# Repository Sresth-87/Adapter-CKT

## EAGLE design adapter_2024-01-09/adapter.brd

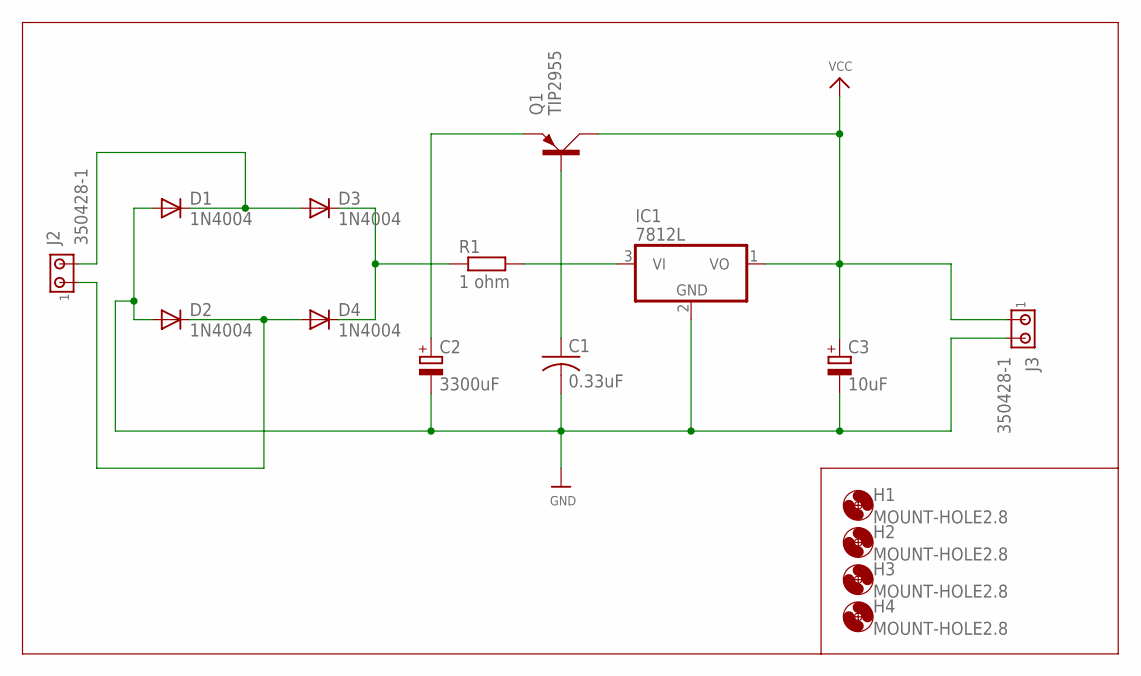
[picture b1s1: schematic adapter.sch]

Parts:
C1: 0.33uF; C025-024X044
C2: 3300uF; CAPPRD508W65D1000H1100B
C3: 10uF; CAPPRD508W65D1000H1100B
D1, D2, D3, D4: 1N4004; DO41-10
H1, H2, H3, H4: MOUNT-HOLE2.8; 2,8
IC1: 7812L; TO92
J2, J3: 350428-1
Q1: TIP2955; TOP3AV
R1: 1 ohm; 0204/7

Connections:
GND: C1.2, C2.2 (-), C3.2 (-), D1.A, D2.A, IC1.2 (GND), J3.2
unnamed: D1.C, D3.A, J2.2
unnamed: D2.C, D4.A, J2.1
unnamed: D3.C, D4.C, R1.1
unnamed: IC1.3 (VI), R1.2
unnamed: C2.1 (+), Q1.E
unnamed: C1.1, Q1.B
VCC: C3.1 (+), IC1.1 (VO), J3.1, Q1.C

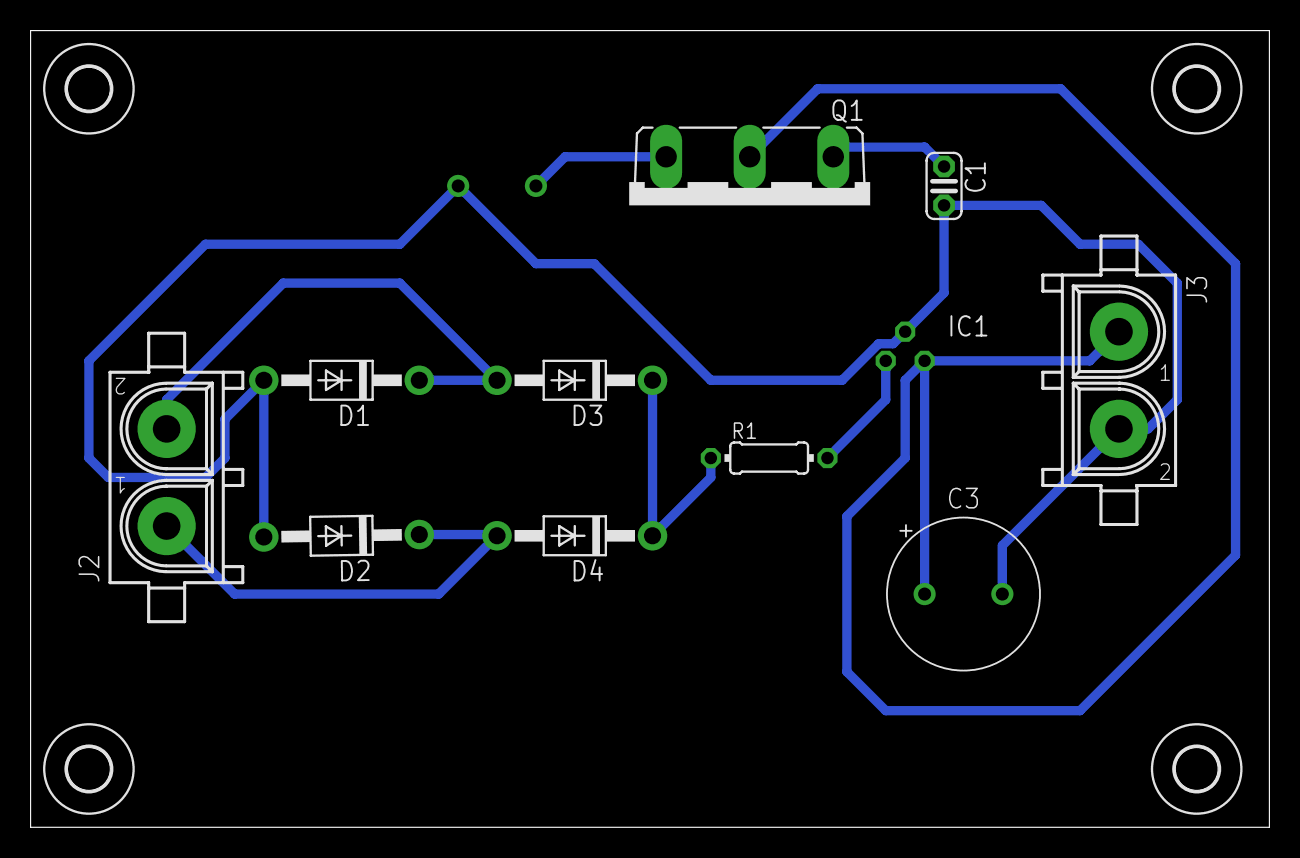
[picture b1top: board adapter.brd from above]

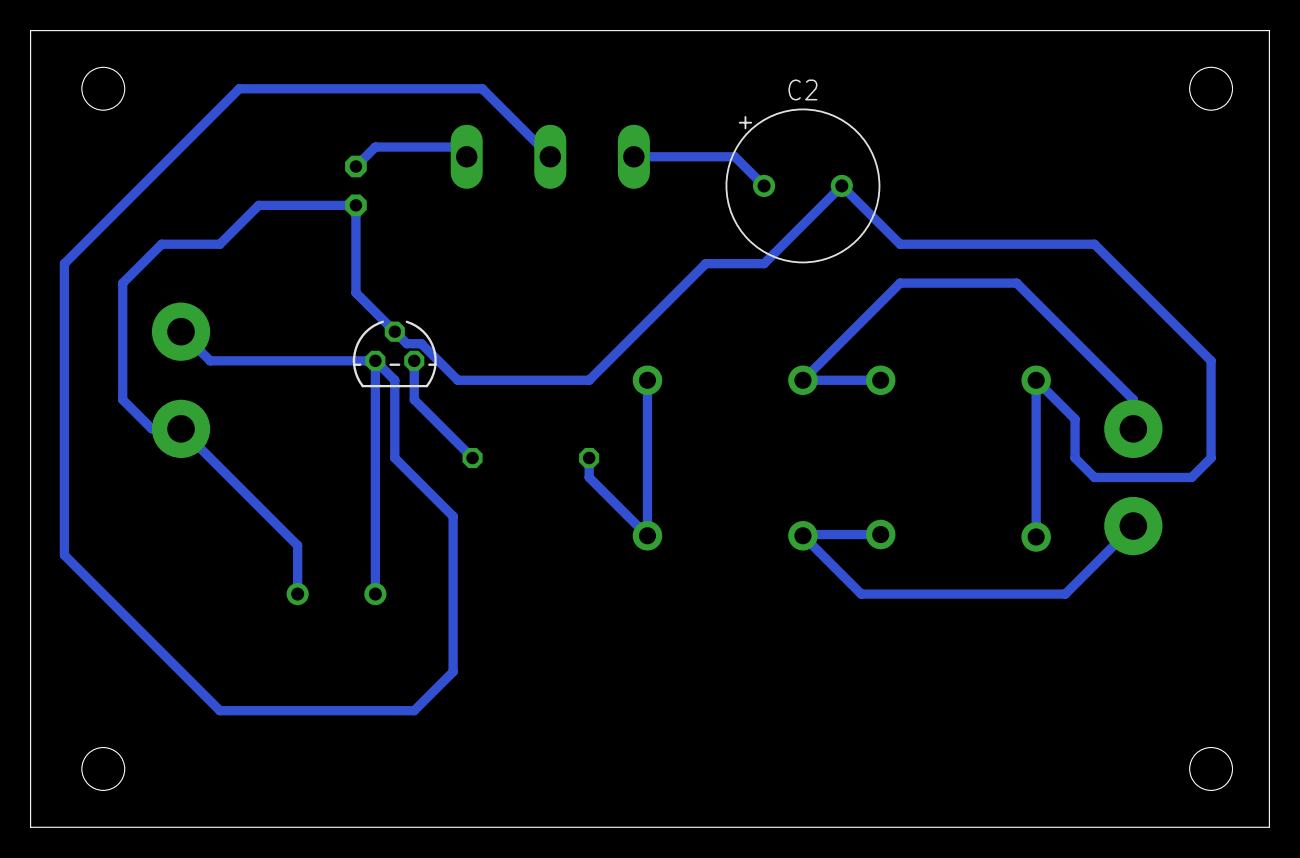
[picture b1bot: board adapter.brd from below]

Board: 2 copper layers, 81.0 x 52.1 mm, 16 parts (2 on the bottom side), 8 nets.
